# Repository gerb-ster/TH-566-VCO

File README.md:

# Thomas Henry 566 VCO

Some years ago I bought a booklet called ‘making music with the 566’ by Thomas Henry. The first time I read it, I understood maybe 10 percent. Since then, every year or so, I’d read it again, and it started making more and more sense. And last year I decided it was time to try and make a PCB for it. So here it is. I’ve added a wave shaper to turn the triangle wave into a saw wave. I made some minor mistakes in the first PCB design, but these are fixed in the schematics below.

## Status: Finished

- done: first schematic & board design
- done: breadboard and test
- done: design frontpanel
- done: order PCB and build prototype

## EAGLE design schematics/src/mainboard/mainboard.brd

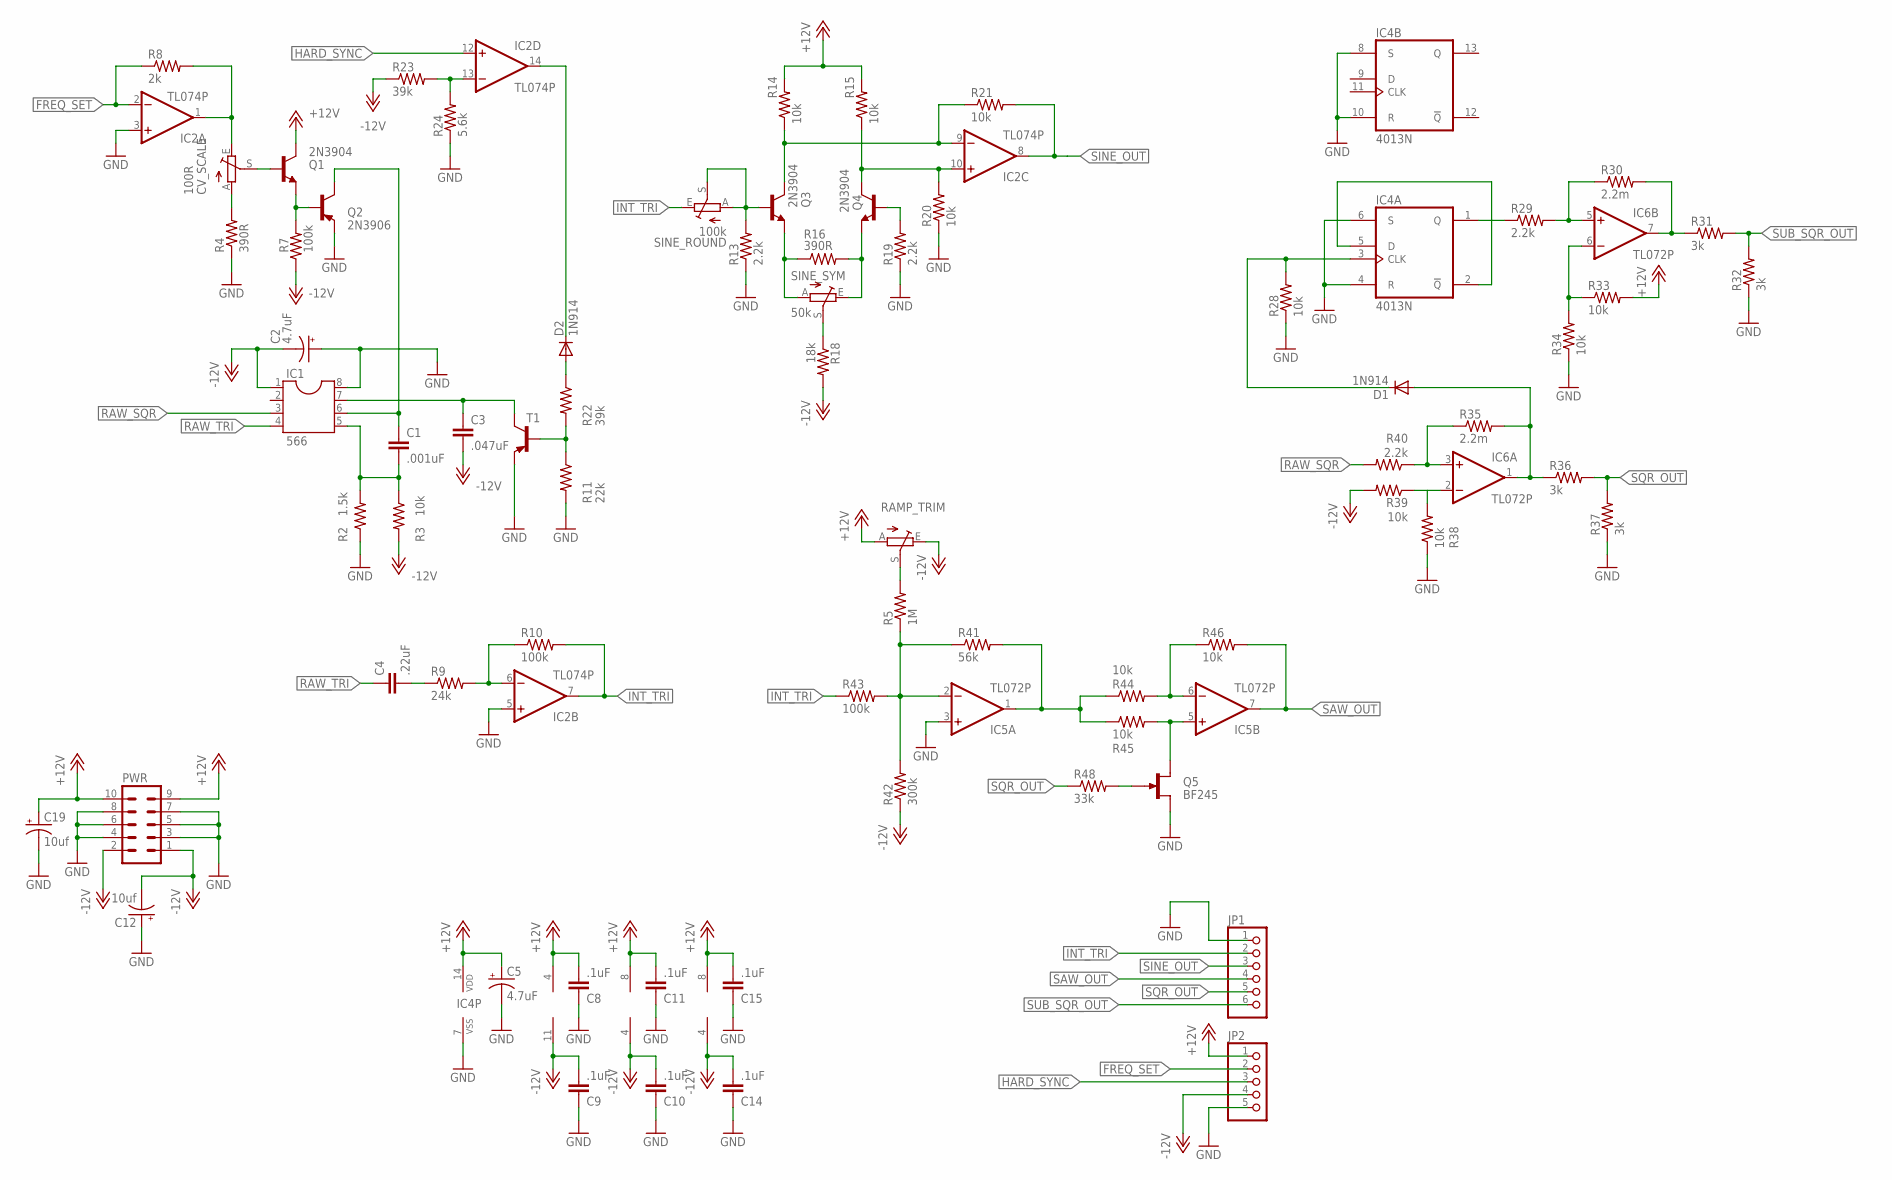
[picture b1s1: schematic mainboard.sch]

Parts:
C1: .001uF; C050-024X044
C2: 4.7uF; E2,5-6
C3: .047uF; C050-024X044
C4: .22uF; C050-024X044
C5: 4.7uF; E2,5-5
C8, C9, C10, C11, C14, C15: .1uF; C050-024X044
C12, C19: 10uf; E2,5-5
CV_SCALE: 100R; RJ9W
D1, D2: 1N914; DO35-7
IC1: 566; DIL08
IC2: TL074P; DIL14
IC4: 4013N; DIL14
IC5, IC6: TL072P; DIL08
JP1: PINHD-1X6; 1X06
JP2: PINHD-1X5; 1X05
PWR: ML10
Q1, Q3, Q4: 2N3904; TO92
Q2: 2N3906; TO92
Q5: BF245; SOT54C
R2: 1.5k; 0204/7
R3, R14, R15, R20, R21, R28, R33, R34, R38, R39, R44, R45, R46: 10k; 0204/7
R4, R16: 390R; 0204/7
R5: 1M; 0204/7
R7, R10, R43: 100k; 0204/7
R8: 2k; 0204/7
R9: 24k; 0204/7
R11: 22k; 0204/7
R13, R19, R29, R40: 2.2k; 0204/7
R18: 18k; 0204/7
R22, R23: 39k; 0204/7
R24: 5.6k; 0204/7
R30, R35: 2.2m; 0204/7
R31, R32, R36, R37: 3k; 0204/7
R41: 56k; 0204/7
R42: 300k; 0204/7
R48: 33k; 0204/7
RAMP_TRIM: TRIM_EU-RJ9W; RJ9W
SINE_ROUND: 100k; RJ9W
SINE_SYM: 50k; RJ9W
T1: 2N3906-PNP-TO92-EBC; TO92-EBC

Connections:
+12V: C5.+, C8.2, C11.2, C15.2, C19.+, IC2.4 (V+), IC4.14 (VDD), IC5.8 (V+), IC6.8 (V+), JP2.1, PWR.9, PWR.10, Q1.1 (C), R14.2, R15.2, R33.2, RAMP_TRIM.A
-12V: C2.-, C3.2, C9.2, C10.2, C12.-, C14.2, IC1.1, IC2.11 (V-), IC5.4 (V-), IC6.4 (V-), JP2.4, PWR.1, PWR.2, R3.2, R7.1, R18.2, R23.1, R39.2, R42.1, RAMP_TRIM.E
FREQ_SET: IC2.2 (-IN), JP2.2, R8.1
GND: C2.+, C5.-, C8.1, C9.1, C10.1, C11.1, C12.+, C14.1, C15.1, C19.-, IC1.8, IC2.3 (+IN), IC2.5 (+IN), IC4.4 (R), IC4.6 (S), IC4.7 (VSS), IC4.8 (S), IC4.10 (R), IC5.3 (+IN), JP1.1, JP2.5, PWR.3, PWR.4, PWR.5, PWR.6, PWR.7, PWR.8, Q2.3 (E), Q5.S, R2.1, R4.1, R11.2, R13.1, R19.1, R20.1, R24.1, R28.1, R32.1, R34.1, R37.1, R38.1, T1.E
HARD_SYNC: IC2.12 (+IN), JP2.3
INT_TRI: IC2.7 (OUT), JP1.2, R10.2, R43.1, SINE_ROUND.E
unnamed: C3.1, IC1.7, T1.C
unnamed: C1.2, IC1.5, R2.2, R3.1
unnamed: C1.1, IC1.6, Q2.1 (C)
unnamed: CV_SCALE.A, R4.2
unnamed: Q1.3 (E), Q2.2 (B), R7.2
unnamed: CV_SCALE.S, Q1.2 (B)
unnamed: CV_SCALE.E, IC2.1 (OUT), R8.2
unnamed: IC2.6 (-IN), R9.2, R10.1
unnamed: C4.2, R9.1
unnamed: IC5.6 (-IN), R44.2, R46.1
unnamed: R11.1, R22.2, T1.B
unnamed: IC4.1 (Q), R29.1
unnamed: IC2.10 (+IN), Q4.1 (C), R15.1, R20.2
unnamed: R18.1, SINE_SYM.S
unnamed: Q3.2 (B), R13.2, SINE_ROUND.A, SINE_ROUND.S
unnamed: IC2.9 (-IN), Q3.1 (C), R14.1, R21.1
unnamed: Q4.2 (B), R19.2
unnamed: Q3.3 (E), R16.1, SINE_SYM.A
unnamed: Q4.3 (E), R16.2, SINE_SYM.E
unnamed: D2.C, IC2.14 (OUT)
unnamed: IC6.5 (+IN), R29.2, R30.1
unnamed: D2.A, R22.1
unnamed: R5.2, RAMP_TRIM.S
unnamed: IC6.6 (-IN), R33.1, R34.2
unnamed: IC4.2 (!Q), IC4.5 (D)
unnamed: D1.C, IC4.3 (CLK), R28.2
unnamed: IC6.7 (OUT), R30.2, R31.1
unnamed: IC5.2 (-IN), R5.1, R41.1, R42.2, R43.2
unnamed: D1.A, IC6.1 (OUT), R35.2, R36.1
unnamed: IC2.13 (-IN), R23.2, R24.2
unnamed: IC6.2 (-IN), R38.2, R39.1
unnamed: IC6.3 (+IN), R35.1, R40.1
unnamed: IC5.1 (OUT), R41.2, R44.1, R45.1
unnamed: IC5.5 (+IN), Q5.D, R45.2
unnamed: Q5.G, R48.2
RAW_SQR: IC1.3, R40.2
RAW_TRI: C4.1, IC1.4
SAW_OUT: IC5.7 (OUT), JP1.4, R46.2
SINE_OUT: IC2.8 (OUT), JP1.3, R21.2
SQR_OUT: JP1.5, R36.2, R37.2, R48.1
SUB_SQR_OUT: JP1.6, R31.2, R32.2

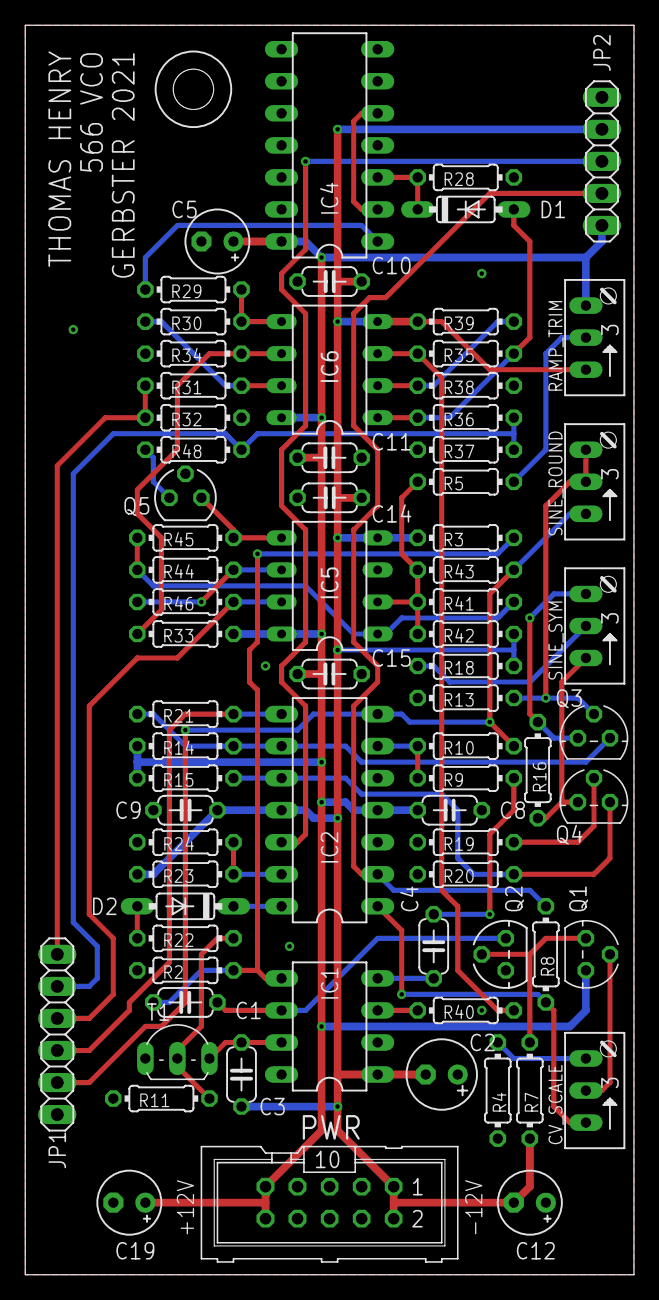
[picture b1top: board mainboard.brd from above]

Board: 2 copper layers, 48.3 x 99.1 mm, 73 parts (0 on the bottom side), 47 nets.

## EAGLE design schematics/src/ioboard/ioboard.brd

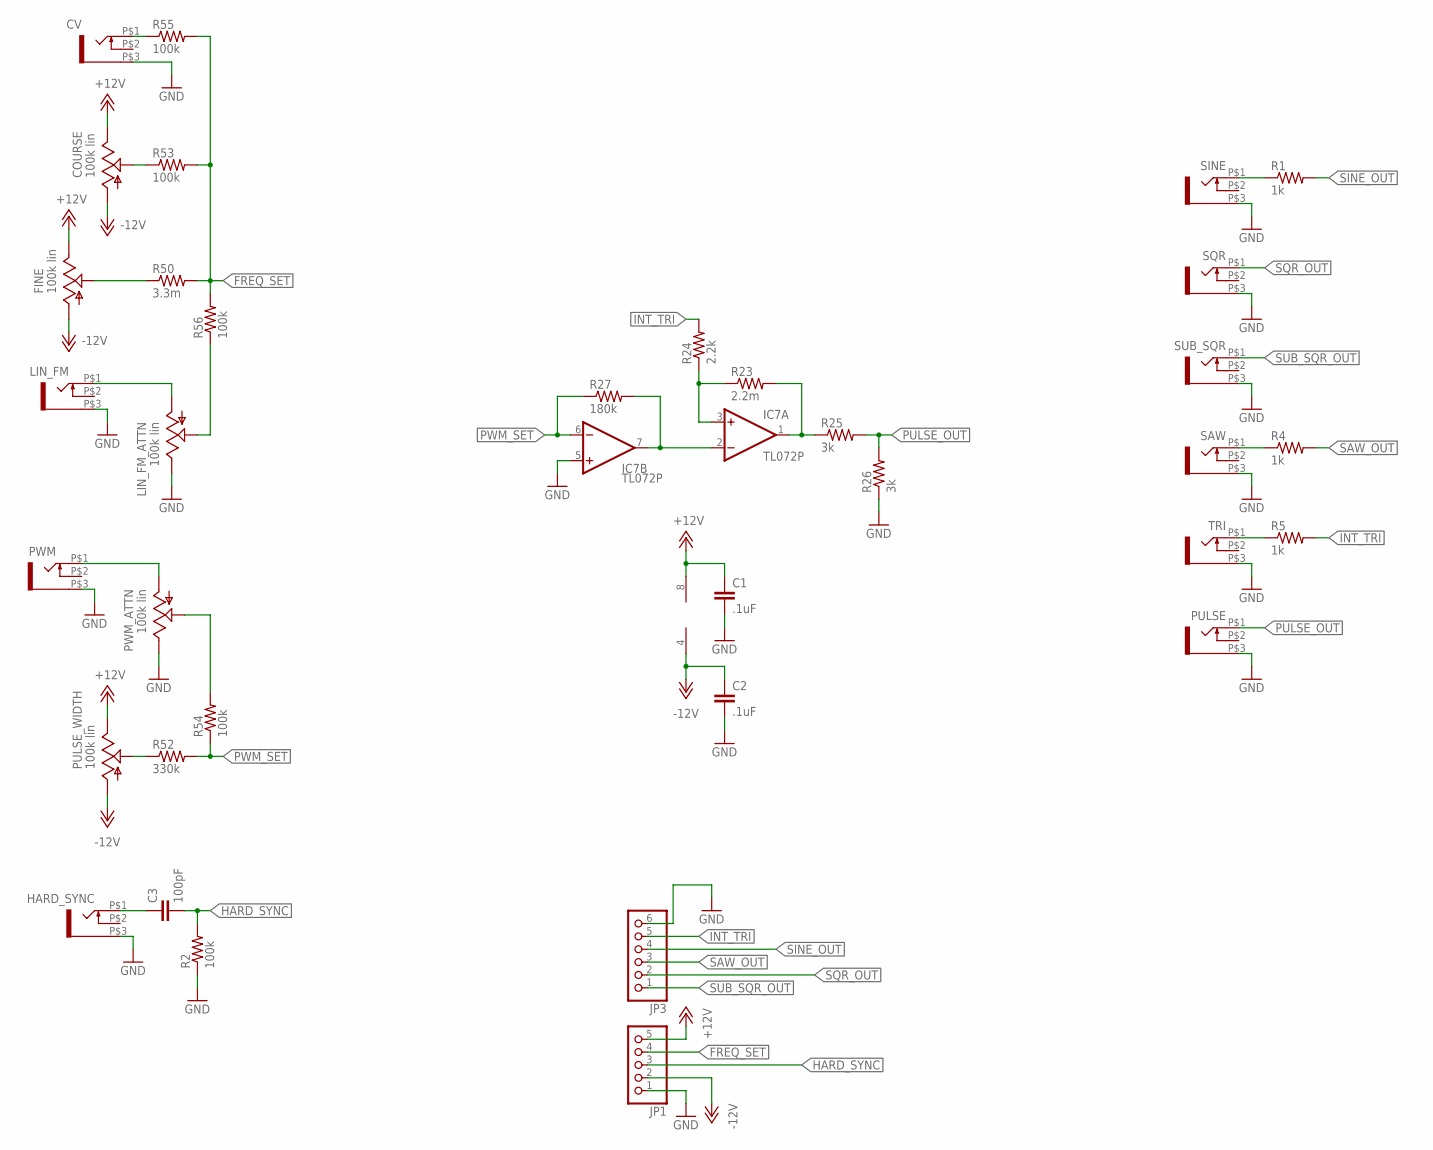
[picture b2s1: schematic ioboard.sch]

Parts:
C1, C2: .1uF; C050-024X044
C3: 100pF; C050-024X044
COURSE: 100k lin; EVUF
CV: WQP-PJ301M-12_JACK
FINE: 100k lin; EVUF
HARD_SYNC: WQP-PJ301M-12_JACK
IC7: TL072P; DIL08
JP1: PINHD-1X5; 1X05
JP3: PINHD-1X6; 1X06
LIN_FM: WQP-PJ301M-12_JACK
LIN_FM_ATTN: 100k lin; EVUF
PULSE: WQP-PJ301M-12_JACK
PULSE_WIDTH: 100k lin; EVUF
PWM: WQP-PJ301M-12_JACK
PWM_ATTN: 100k lin; EVUF
R1, R4, R5: 1k; 0204/7
R2, R53, R54, R55, R56: 100k; 0204/7
R23: 2.2m; 0204/7
R24: 2.2k; 0204/7
R25, R26: 3k; 0204/7
R27: 180k; 0204/7
R50: 3.3m; 0204/7
R52: 330k; 0204/7
SAW: WQP-PJ301M-12_JACK
SINE: WQP-PJ301M-12_JACK
SQR: WQP-PJ301M-12_JACK
SUB_SQR: WQP-PJ301M-12_JACK
TRI: WQP-PJ301M-12_JACK

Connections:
+12V: C1.1, COURSE.3 (E), FINE.3 (E), IC7.8 (V+), JP1.5, PULSE_WIDTH.3 (E)
-12V: C2.1, COURSE.1 (A), FINE.1 (A), IC7.4 (V-), JP1.2, PULSE_WIDTH.1 (A)
FREQ_SET: JP1.4, R50.2, R53.2, R55.2, R56.2
GND: C1.2, C2.2, CV.P$3 (1), HARD_SYNC.P$3 (1), IC7.5 (+IN), JP1.1, JP3.6, LIN_FM.P$3 (1), LIN_FM_ATTN.3 (E), PULSE.P$3 (1), PWM.P$3 (1), PWM_ATTN.3 (E), R2.1, R26.1, SAW.P$3 (1), SINE.P$3 (1), SQR.P$3 (1), SUB_SQR.P$3 (1), TRI.P$3 (1)
HARD_SYNC: C3.2, JP1.3, R2.2
INT_TRI: JP3.5, R5.2, R24.2
IO_PWM_IN: PWM_ATTN.2 (S), R54.2
unnamed: R1.1, SINE.P$1 (2)
unnamed: R5.1, TRI.P$1 (2)
unnamed: R4.1, SAW.P$1 (2)
unnamed: C3.1, HARD_SYNC.P$1 (2)
unnamed: IC7.1 (OUT), R23.2, R25.1
unnamed: IC7.2 (-IN), IC7.7 (OUT), R27.2
unnamed: IC7.3 (+IN), R23.1, R24.1
unnamed: PWM.P$1 (2), PWM_ATTN.1 (A)
unnamed: PULSE_WIDTH.2 (S), R52.1
unnamed: FINE.2 (S), R50.1
unnamed: COURSE.2 (S), R53.1
unnamed: CV.P$1 (2), R55.1
unnamed: LIN_FM.P$1 (2), LIN_FM_ATTN.1 (A)
unnamed: LIN_FM_ATTN.2 (S), R56.1
PULSE_OUT: PULSE.P$1 (2), R25.2, R26.2
PWM_SET: IC7.6 (-IN), R27.1, R52.2, R54.1
SAW_OUT: JP3.3, R4.2
SINE_OUT: JP3.4, R1.2
SQR_OUT: JP3.2, SQR.P$1 (2)
SUB_SQR_OUT: JP3.1, SUB_SQR.P$1 (2)

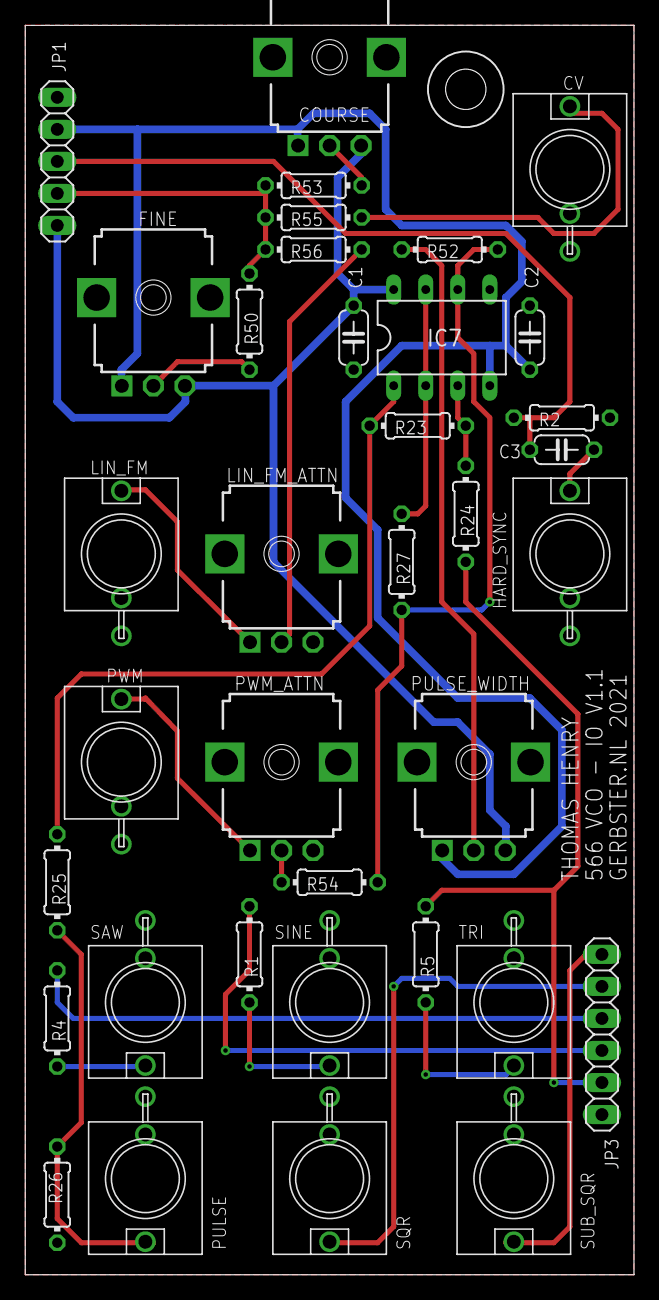
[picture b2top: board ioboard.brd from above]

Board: 2 copper layers, 48.3 x 99.1 mm, 36 parts (0 on the bottom side), 27 nets.

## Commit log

2021-05-06 some files
2021-05-07 Added files & structure
2021-05-10 Added Status
2021-05-11 Added Status & Images
2021-06-15 Updated Schematics, Fixed Power Socket orientation
2021-07-19 Fixed minor issues, added documentation and updated some faceplates
2021-08-06 Updated some schematics and docs
2021-08-10 Fixed some bugs and updated documentation
2021-08-10 Update CHANGELOG.md
    fixed date..
2022-04-20 Some updates & bugfixes
2022-04-22 Fixed schematics & descriptions
2022-05-17 Updated Firmware
2022-05-18 Updated Faceplates
2022-05-18 Fixed issues
2022-05-21 Fixed schematics
2022-05-28 General updates
